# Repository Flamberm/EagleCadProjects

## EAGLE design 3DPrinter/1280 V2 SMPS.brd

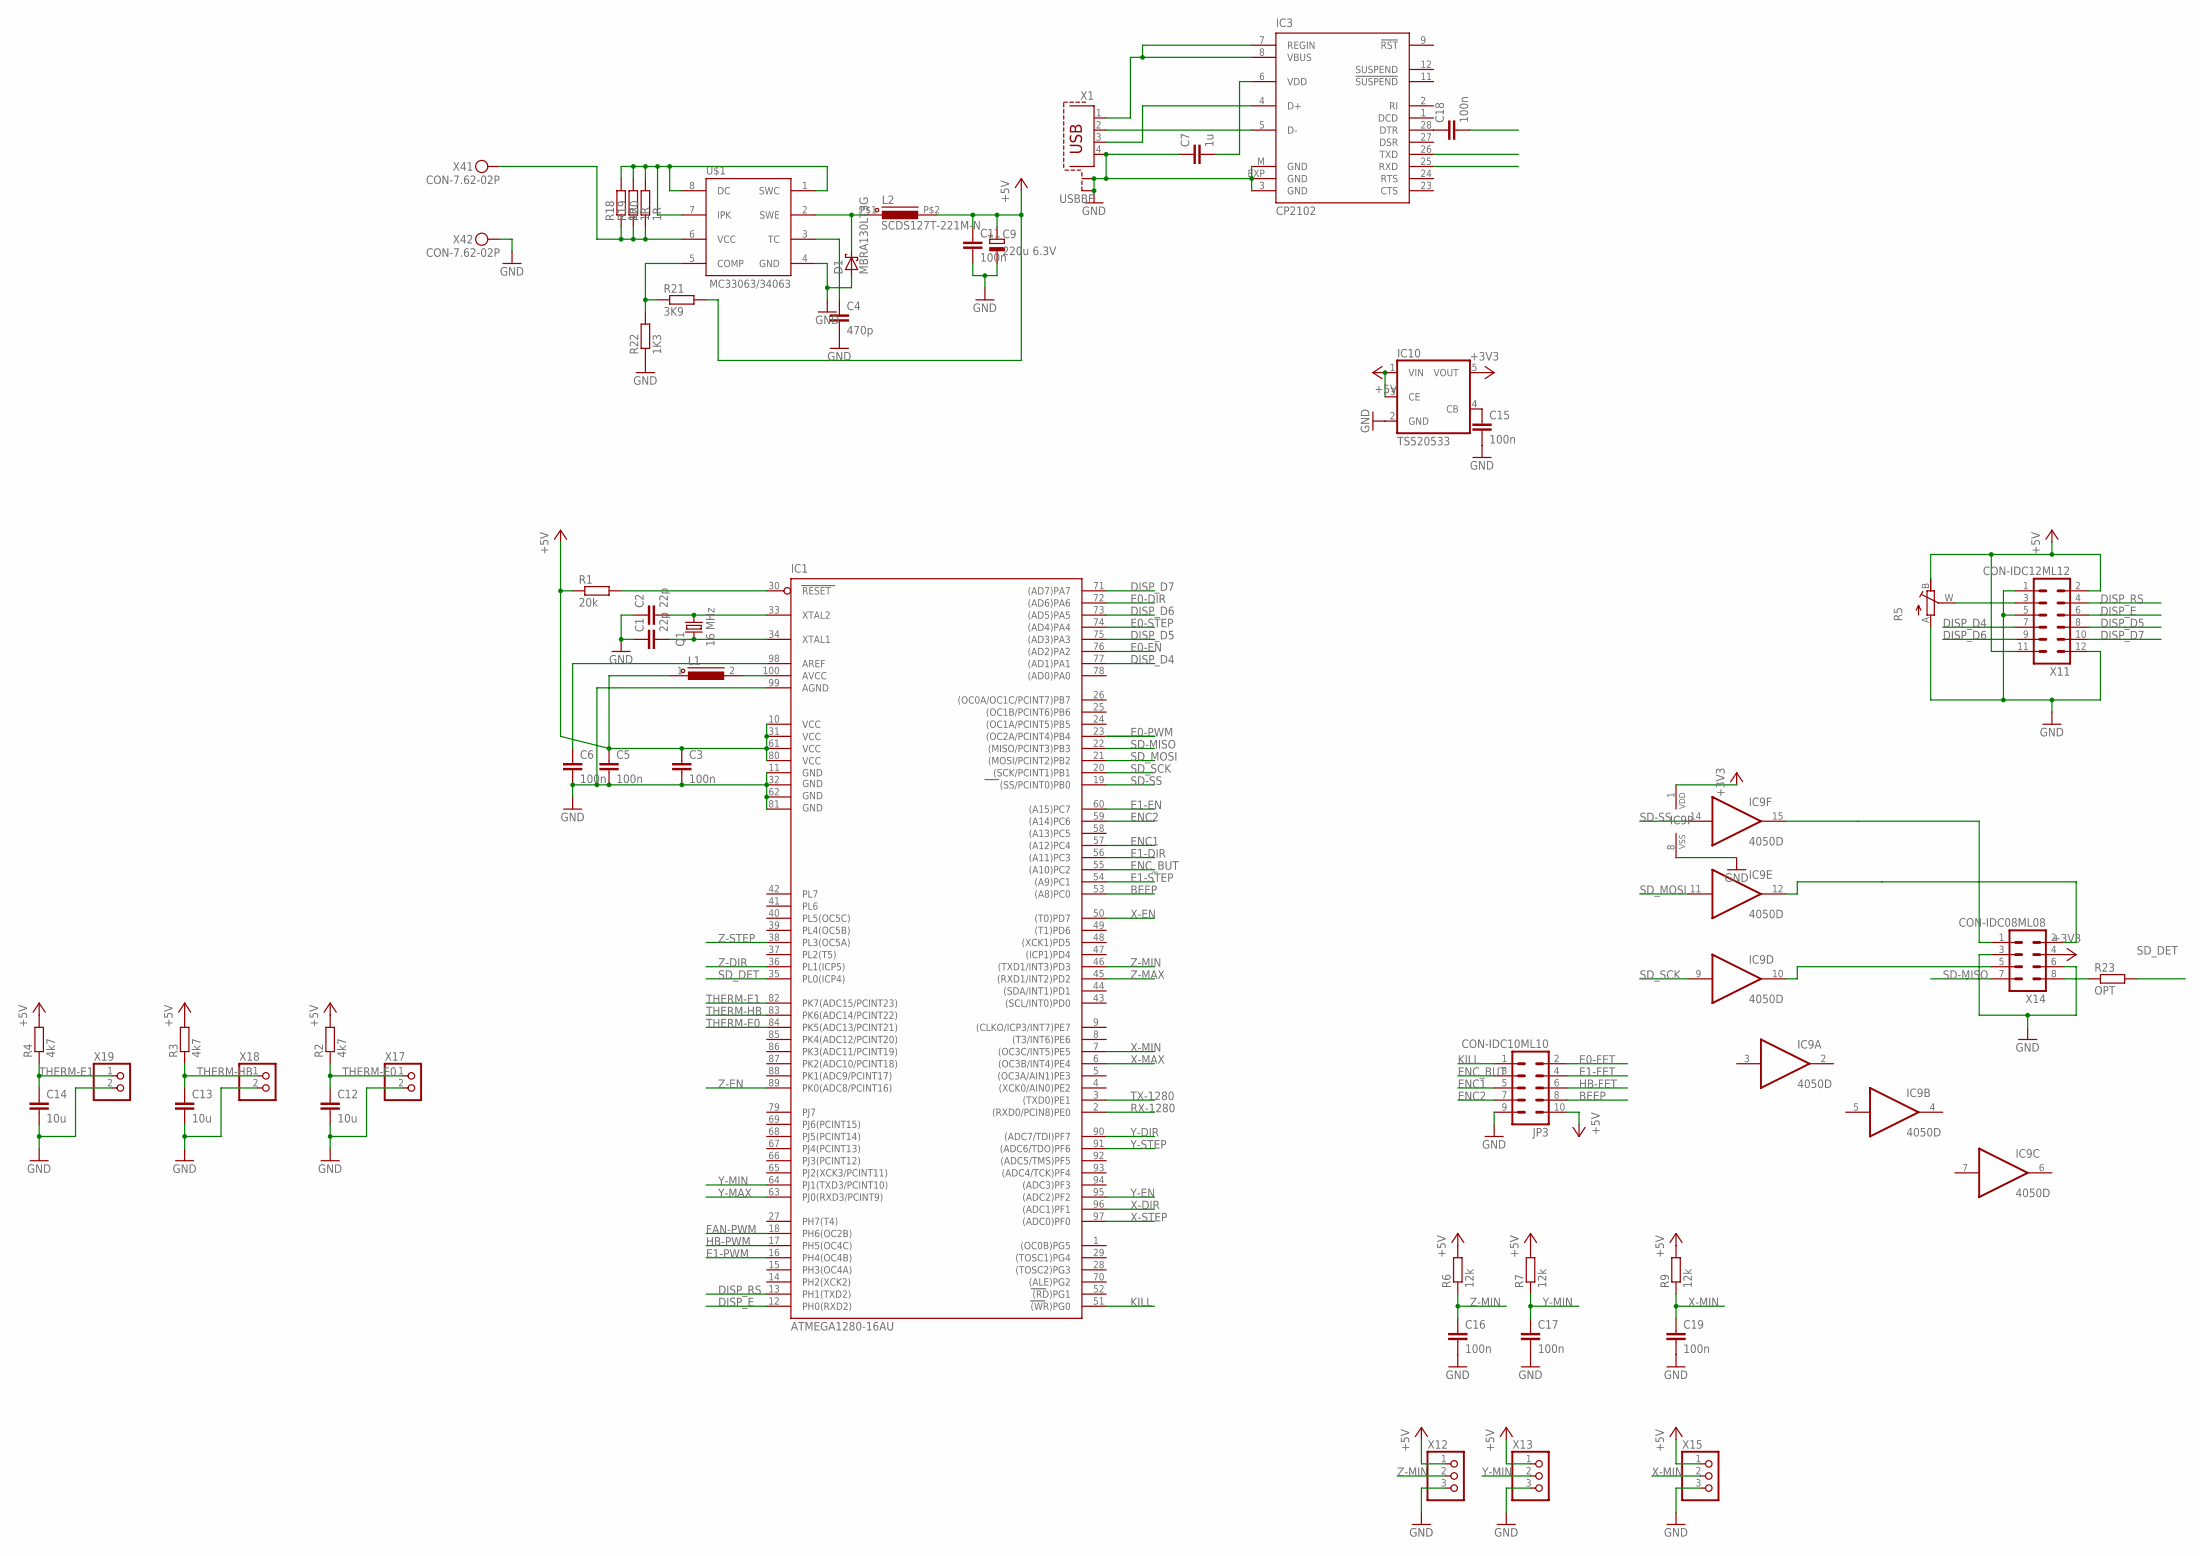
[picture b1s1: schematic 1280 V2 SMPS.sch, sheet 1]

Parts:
C1, C2: 22p; C0805
C3, C5, C6, C11, C15, C16, C17, C18, C19: 100n; C0805
C4: 470p; C0805
C7: 1u; C0805
C9: 220u 6.3V; 153CLV-0605
C12, C13, C14: 10u; C1210
D1: MBRA130LT3G; DO214AC
IC1: ATMEGA1280-16AU; TQFP100
IC3: CP2102; MLP28
IC9: 4050D; SO16
IC10: TS520533; SOT25
JP3: CON-IDC10ML10; ML10
L1: INDUCTOR1210; C1210
L2: SCDS127T-221M-N; SCD-0705
Q1: 16 MHz; CRYSTAL-3225
R1: 20k; R0805
R2, R3, R4: 4k7; R0805
R5: R_POTTURN-X; RJ9W
R6, R7, R9: 12k; R0805
R18, R19, R20: 1R; R0805
R21: 3K9; R0805
R22: 1K3; R0805
R23: OPT; R0805
U$1: MC33063/MC34063D; SO08
X1: USBBF; PN61729-S
X4: CON-7.62-02P; KF25C-7.62-02P-13
X11: CON-IDC12ML12; ML12
X12, X13, X15: PINHD-1X3; 1X03
X14: CON-IDC08ML08; ML08
X17, X18, X19: PINHD-1X2; 1X02

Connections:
!RST: C18.2, IC1.30 (RESET), R1.2
+3V3: IC9.1 (VDD), IC10.5 (VOUT), X14.4
+5V: C3.1, C5.1, C9.+, C11.1, IC1.10 (VCC), IC1.31 (VCC1), IC1.61 (VCC2), IC1.80 (VCC3), IC10.1 (VIN), IC10.3 (CE), JP3.10, L1.1, L2.P$2 (2), R1.1, R2.2, R3.2, R4.2, R5.B (E), R6.2, R7.2, R9.2, R21.2, X11.2, X11.11, X12.1, X13.1, X15.1; also elsewhere on the board
AREF: C6.1, IC1.98 (AREF)
AVCC: IC1.100 (AVCC), L1.2
BEEP: IC1.53 ((A8)PC0), JP3.8
DISP_D4: IC1.77 ((AD1)PA1), X11.7
DISP_D5: IC1.75 ((AD3)PA3), X11.8
DISP_D6: IC1.73 ((AD5)PA5), X11.9
DISP_D7: IC1.71 ((AD7)PA7), X11.10
DISP_E: IC1.12 (PH0(RXD2)), X11.6
DISP_RS: IC1.13 (PH1(TXD2)), X11.4
E0-DIR: IC1.72 ((AD6)PA6); also elsewhere on the board
E0-EN: IC1.76 ((AD2)PA2); also elsewhere on the board
E0-FET: JP3.2; also elsewhere on the board
E0-PWM: IC1.23 ((OC2A/PCINT4)PB4); also elsewhere on the board
E0-STEP: IC1.74 ((AD4)PA4); also elsewhere on the board
E1-DIR: IC1.56 ((A11)PC3); also elsewhere on the board
E1-EN: IC1.60 ((A15)PC7); also elsewhere on the board
E1-FET: JP3.4; also elsewhere on the board
E1-PWM: IC1.16 (PH4(OC4B)); also elsewhere on the board
E1-STEP: IC1.54 ((A9)PC1); also elsewhere on the board
ENC1: IC1.57 ((A12)PC4), JP3.5
ENC2: IC1.59 ((A14)PC6), JP3.7
ENC_BUT: IC1.55 ((A10)PC2), JP3.3
FAN-PWM: IC1.18 (PH6(OC2B)); also elsewhere on the board
GND: C1.1, C2.1, C3.2, C4.2, C5.2, C6.2, C7.1, C9.-, C11.2, C12.2, C13.2, C14.2, C15.2, C16.2, C17.2, C19.2, D1.A, IC1.11 (GND), IC1.32 (GND1), IC1.62 (GND2), IC1.81 (GND3), IC1.99 (AGND), IC3.3 (GND), IC3.EXP (GND), IC3.M (GND), IC9.8 (VSS), IC10.2 (GND), JP3.9, R5.A, R22.1, U$1.4 (GND), X1.4 (GND), X1.S1, X1.S2, X4.P$2, X11.1, X11.5, X11.12, X12.3, X13.3, X14.3, X14.6, X15.3, X17.2, X18.2, X19.2; also elsewhere on the board
HB-FET: JP3.6; also elsewhere on the board
HB-PWM: IC1.17 (PH5(OC4C)); also elsewhere on the board
KILL: IC1.51 ((WR)PG0), JP3.1
unnamed: IC3.5 (D-), X1.2 (D-)
unnamed: IC3.4 (D+), X1.3 (D+)
unnamed: C7.2, IC3.6 (VDD)
unnamed: C18.1, IC3.28 (DTR)
unnamed: IC3.7 (REGIN), IC3.8 (VBUS), X1.1 (VCC)
unnamed: R5.W (S), X11.3
unnamed: R23.1, X14.8
unnamed: IC9.15 (O), X14.1
unnamed: IC9.12 (O), X14.2
unnamed: IC9.10 (O), X14.5
unnamed: C15.1, IC10.4 (CB)
unnamed: R18.2, R19.2, R20.2, U$1.1 (SWC), U$1.7 (IPK), U$1.8 (DC)
unnamed: D1.C, L2.P$1 (1), U$1.2 (SWE)
unnamed: C4.1, U$1.3 (TC)
unnamed: R21.1, R22.2, U$1.5 (COMP)
RX-1280: IC1.2 ((RXD0/PCIN8)PE0), IC3.26 (TXD)
SD-MISO: IC1.22 ((MISO/PCINT3)PB3), X14.7
SD-SS: IC1.19 ((SS/PCINT0)PB0), IC9.14 (I)
SD_DET: IC1.35 (PL0(ICP4)), R23.2
SD_MOSI: IC1.21 ((MOSI/PCINT2)PB2), IC9.11 (I)
SD_SCK: IC1.20 ((SCK/PCINT1)PB1), IC9.9 (I)
THERM-E0: C12.1, IC1.84 (PK5(ADC13/PCINT21)), R2.1, X17.1
THERM-E1: C14.1, IC1.82 (PK7(ADC15/PCINT23)), R4.1, X19.1
THERM-HB: C13.1, IC1.83 (PK6(ADC14/PCINT22)), R3.1, X18.1
TX-1280: IC1.3 ((TXD0)PE1), IC3.25 (RXD)
V-IN: R18.1, R19.1, R20.1, U$1.6 (VCC), X4.P$1; also elsewhere on the board
X-DIR: IC1.96 ((ADC1)PF1); also elsewhere on the board
X-EN: IC1.50 ((T0)PD7); also elsewhere on the board
X-MAX: IC1.6 ((OC3B/INT4)PE4)
X-MIN: C19.1, IC1.7 ((OC3C/INT5)PE5), R9.1, X15.2
X-STEP: IC1.97 ((ADC0)PF0); also elsewhere on the board
XTAL1: C1.2, IC1.34 (XTAL1), Q1.P$2 (1)
XTAL2: C2.2, IC1.33 (XTAL2), Q1.P$4 (2)
Y-DIR: IC1.90 ((ADC7/TDI)PF7); also elsewhere on the board
Y-EN: IC1.95 ((ADC2)PF2); also elsewhere on the board
Y-MAX: IC1.63 (PJ0(RXD3/PCINT9))
Y-MIN: C17.1, IC1.64 (PJ1(TXD3/PCINT10)), R7.1, X13.2
Y-STEP: IC1.91 ((ADC6/TDO)PF6); also elsewhere on the board
Z-DIR: IC1.36 (PL1(ICP5)); also elsewhere on the board
Z-EN: IC1.89 (PK0(ADC8/PCINT16)); also elsewhere on the board
Z-MAX: IC1.45 ((RXD1/INT2)PD2)
Z-MIN: C16.1, IC1.46 ((TXD1/INT3)PD3), R6.1, X12.2
Z-STEP: IC1.38 (PL3(OC5A)); also elsewhere on the board

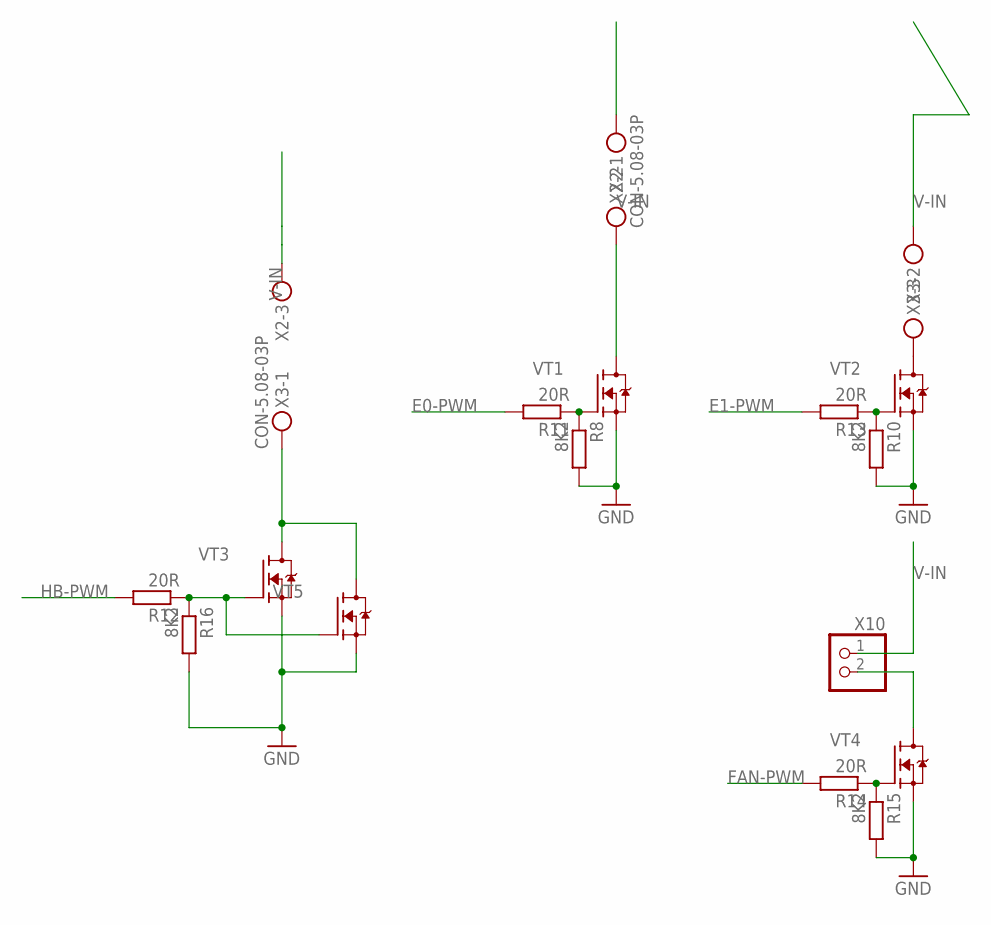
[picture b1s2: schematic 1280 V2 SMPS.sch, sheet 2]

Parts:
R8, R10, R15, R16: 8K2; R0805
R11, R12, R13, R14: 20R; R0805
VT1, VT2, VT3, VT4, VT5: FET-NPF-6X5; POWERFLAT-5X6
X2, X3: CON-5.08-03P; MKDSN1,5/3-5,08
X10: PINHD-1X2; 1X02

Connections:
E0-: VT1.D1 (D), X2.2
E0-FET: R8.1, R11.1, VT1.G; also elsewhere on the board
E0-PWM: R11.2; also elsewhere on the board
E1-FET: R10.1, R13.1, VT2.G; also elsewhere on the board
E1-PWM: R13.2; also elsewhere on the board
FAN-: VT4.D1 (D), X10.2
FAN-PWM: R14.2; also elsewhere on the board
GND: R8.2, R10.2, R15.2, R16.2, VT1.S1 (S), VT1.S2 (S), VT1.S3 (S), VT2.S1 (S), VT2.S2 (S), VT2.S3 (S), VT3.S1 (S), VT3.S2 (S), VT3.S3 (S), VT4.S1 (S), VT4.S2 (S), VT4.S3 (S), VT5.S1 (S), VT5.S2 (S), VT5.S3 (S); also elsewhere on the board
HB-: VT3.D1 (D), VT5.D1 (D), X3.1
HB-FET: R12.1, R16.1, VT3.G, VT5.G; also elsewhere on the board
HB-PWM: R12.2; also elsewhere on the board
unnamed: R14.1, R15.1, VT4.G
unnamed: VT2.D1 (D), X3.3
V-IN: X2.1, X2.3, X3.2, X10.1; also elsewhere on the board

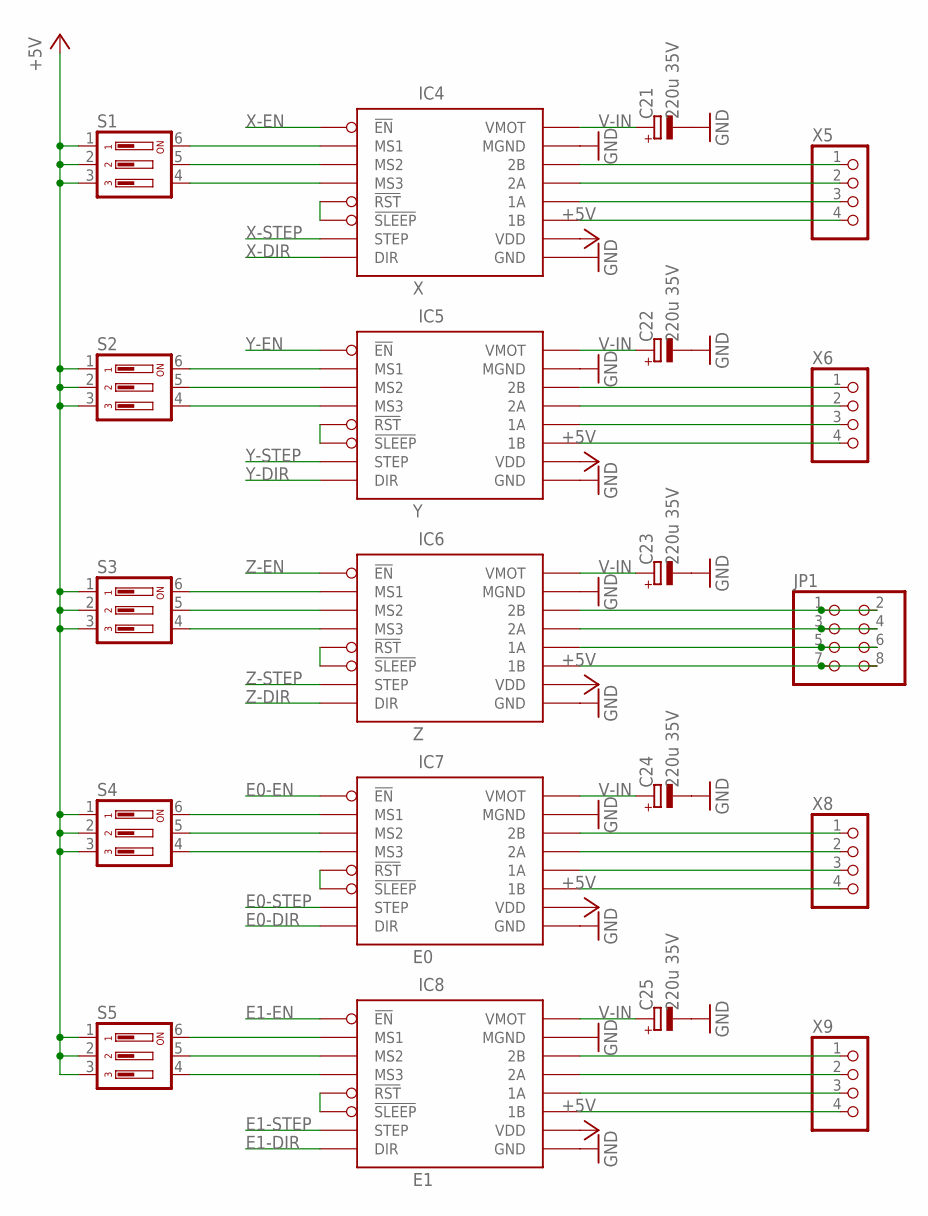
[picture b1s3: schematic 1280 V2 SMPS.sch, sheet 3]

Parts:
C21, C22, C23, C24, C25: 220u 35V; E3.5-8-11H
IC4: X; DRV-BRK
IC5: Y; DRV-BRK
IC6: Z; DRV-BRK
IC7: E0; DRV-BRK
IC8: E1; DRV-BRK
JP1: PINHD-2X4/90; 2X04/90
S1, S2, S3, S4, S5: SW-DIP03S; DIP03YL
X5, X6, X8, X9: PINHD-1X4/90; 1X04/90

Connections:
+5V: IC4.P$10 (VDD), IC5.P$10 (VDD), IC6.P$10 (VDD), IC7.P$10 (VDD), IC8.P$10 (VDD), S1.1, S1.2, S1.3, S2.1, S2.2, S2.3, S3.1, S3.2, S3.3, S4.1, S4.2, S4.3, S5.1, S5.2, S5.3; also elsewhere on the board
E0-DIR: IC7.P$8 (DIR); also elsewhere on the board
E0-EN: IC7.P$1 (!EN); also elsewhere on the board
E0-STEP: IC7.P$7 (STEP); also elsewhere on the board
E1-DIR: IC8.P$8 (DIR); also elsewhere on the board
E1-EN: IC8.P$1 (!EN); also elsewhere on the board
E1-STEP: IC8.P$7 (STEP); also elsewhere on the board
GND: C21.-, C22.-, C23.-, C24.-, C25.-, IC4.P$9 (GND), IC4.P$15 (MGND), IC5.P$9 (GND), IC5.P$15 (MGND), IC6.P$9 (GND), IC6.P$15 (MGND), IC7.P$9 (GND), IC7.P$15 (MGND), IC8.P$9 (GND), IC8.P$15 (MGND); also elsewhere on the board
unnamed: IC4.P$14 (2B), X5.1
unnamed: IC4.P$13 (2A), X5.2
unnamed: IC4.P$12 (1A), X5.3
unnamed: IC4.P$5 (!RST), IC4.P$6 (!SLEEP)
unnamed: IC5.P$5 (!RST), IC5.P$6 (!SLEEP)
unnamed: IC4.P$11 (1B), X5.4
unnamed: IC7.P$5 (!RST), IC7.P$6 (!SLEEP)
unnamed: IC6.P$5 (!RST), IC6.P$6 (!SLEEP)
unnamed: IC5.P$14 (2B), X6.1
unnamed: IC5.P$13 (2A), X6.2
unnamed: IC8.P$5 (!RST), IC8.P$6 (!SLEEP)
unnamed: IC5.P$12 (1A), X6.3
unnamed: IC5.P$11 (1B), X6.4
unnamed: IC6.P$14 (2B), JP1.1, JP1.2
unnamed: IC6.P$13 (2A), JP1.3, JP1.4
unnamed: IC6.P$12 (1A), JP1.5, JP1.6
unnamed: IC6.P$11 (1B), JP1.7, JP1.8
unnamed: IC7.P$14 (2B), X8.1
unnamed: IC7.P$13 (2A), X8.2
unnamed: IC7.P$12 (1A), X8.3
unnamed: IC7.P$11 (1B), X8.4
unnamed: IC8.P$14 (2B), X9.1
unnamed: IC8.P$13 (2A), X9.2
unnamed: IC8.P$12 (1A), X9.3
unnamed: IC8.P$11 (1B), X9.4
unnamed: IC4.P$4 (MS3), S1.4
unnamed: IC4.P$3 (MS2), S1.5
unnamed: IC4.P$2 (MS1), S1.6
unnamed: IC5.P$2 (MS1), S2.6
unnamed: IC5.P$3 (MS2), S2.5
unnamed: IC5.P$4 (MS3), S2.4
unnamed: IC6.P$2 (MS1), S3.6
unnamed: IC6.P$3 (MS2), S3.5
unnamed: IC6.P$4 (MS3), S3.4
unnamed: IC7.P$2 (MS1), S4.6
unnamed: IC7.P$3 (MS2), S4.5
unnamed: IC7.P$4 (MS3), S4.4
unnamed: IC8.P$2 (MS1), S5.6
unnamed: IC8.P$3 (MS2), S5.5
unnamed: IC8.P$4 (MS3), S5.4
V-IN: C21.+, C22.+, C23.+, C24.+, C25.+, IC4.P$16 (VMOT), IC5.P$16 (VMOT), IC6.P$16 (VMOT), IC7.P$16 (VMOT), IC8.P$16 (VMOT); also elsewhere on the board
X-DIR: IC4.P$8 (DIR); also elsewhere on the board
X-EN: IC4.P$1 (!EN); also elsewhere on the board
X-STEP: IC4.P$7 (STEP); also elsewhere on the board
Y-DIR: IC5.P$8 (DIR); also elsewhere on the board
Y-EN: IC5.P$1 (!EN); also elsewhere on the board
Y-STEP: IC5.P$7 (STEP); also elsewhere on the board
Z-DIR: IC6.P$8 (DIR); also elsewhere on the board
Z-EN: IC6.P$1 (!EN); also elsewhere on the board
Z-STEP: IC6.P$7 (STEP); also elsewhere on the board

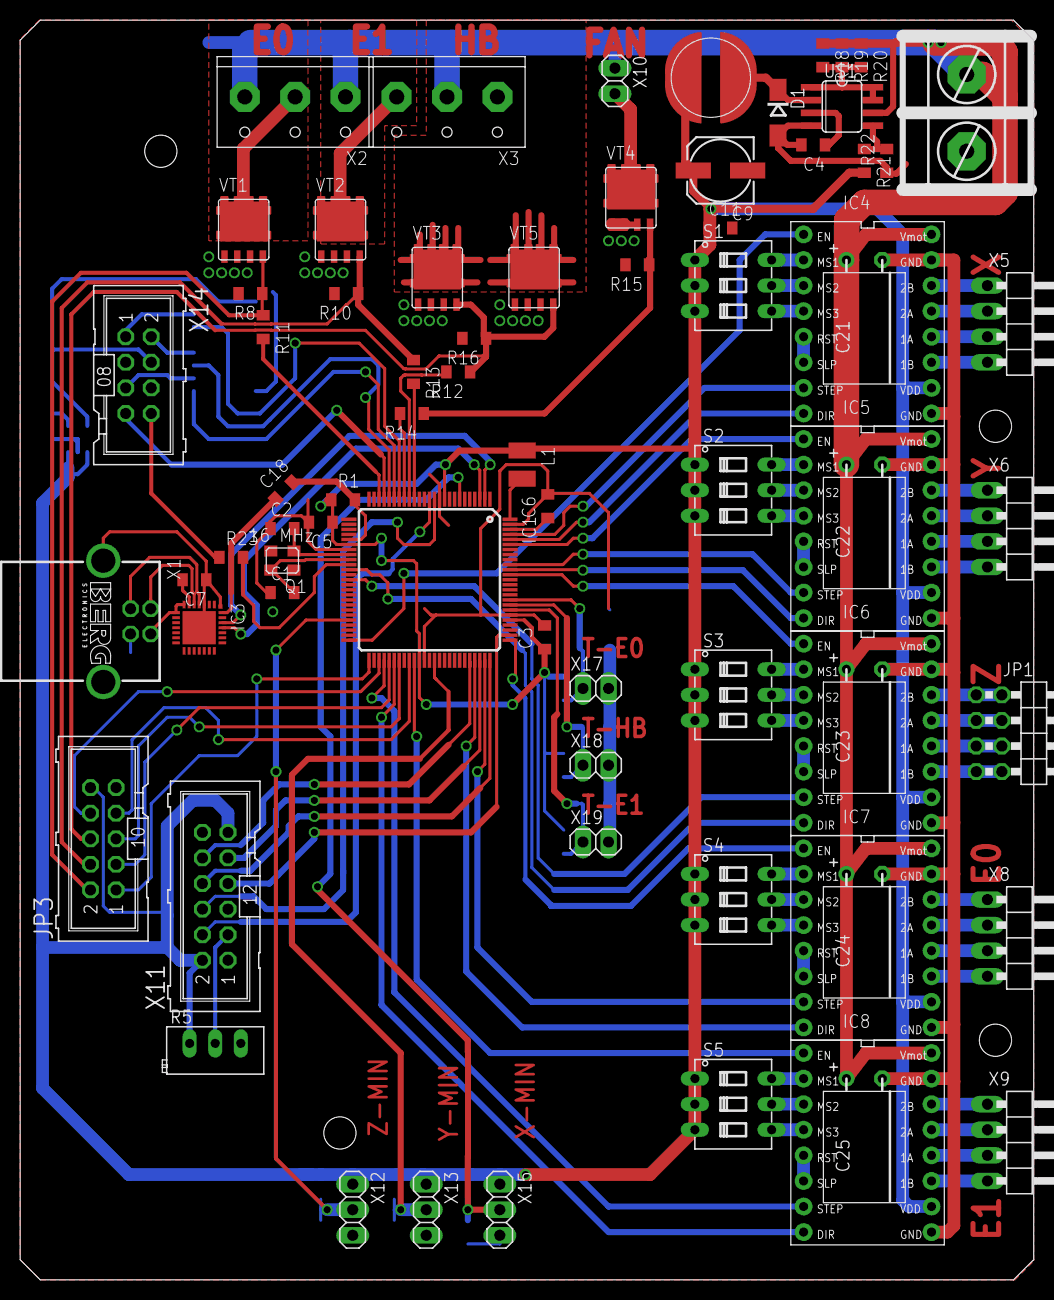
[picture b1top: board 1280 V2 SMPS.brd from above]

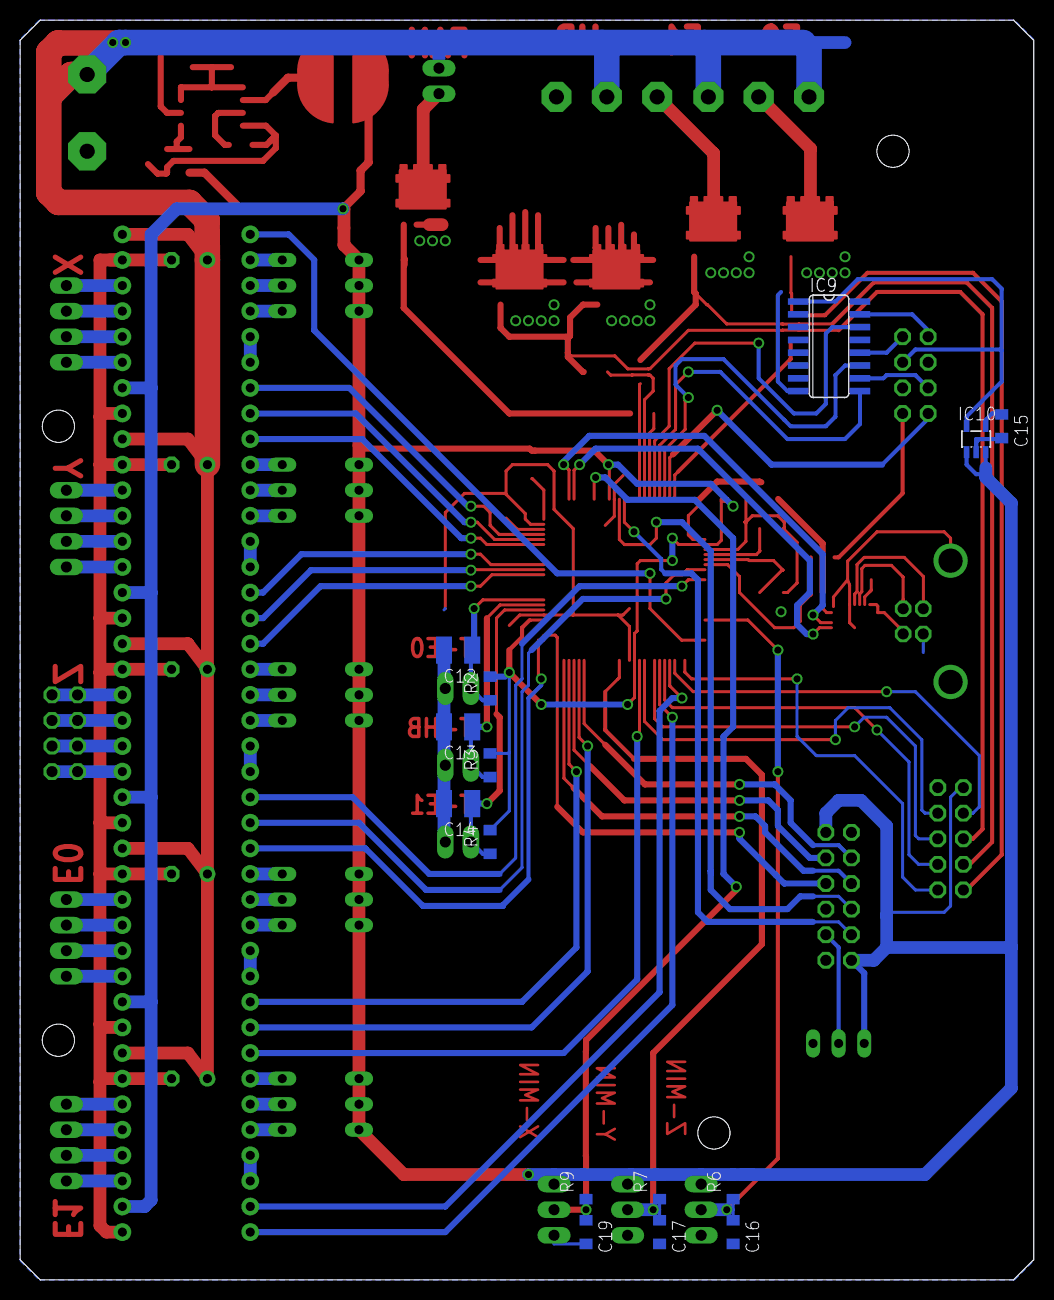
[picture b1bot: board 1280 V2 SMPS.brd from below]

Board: 2 copper layers, 100.6 x 125.1 mm, 87 parts (15 on the bottom side), 115 nets.

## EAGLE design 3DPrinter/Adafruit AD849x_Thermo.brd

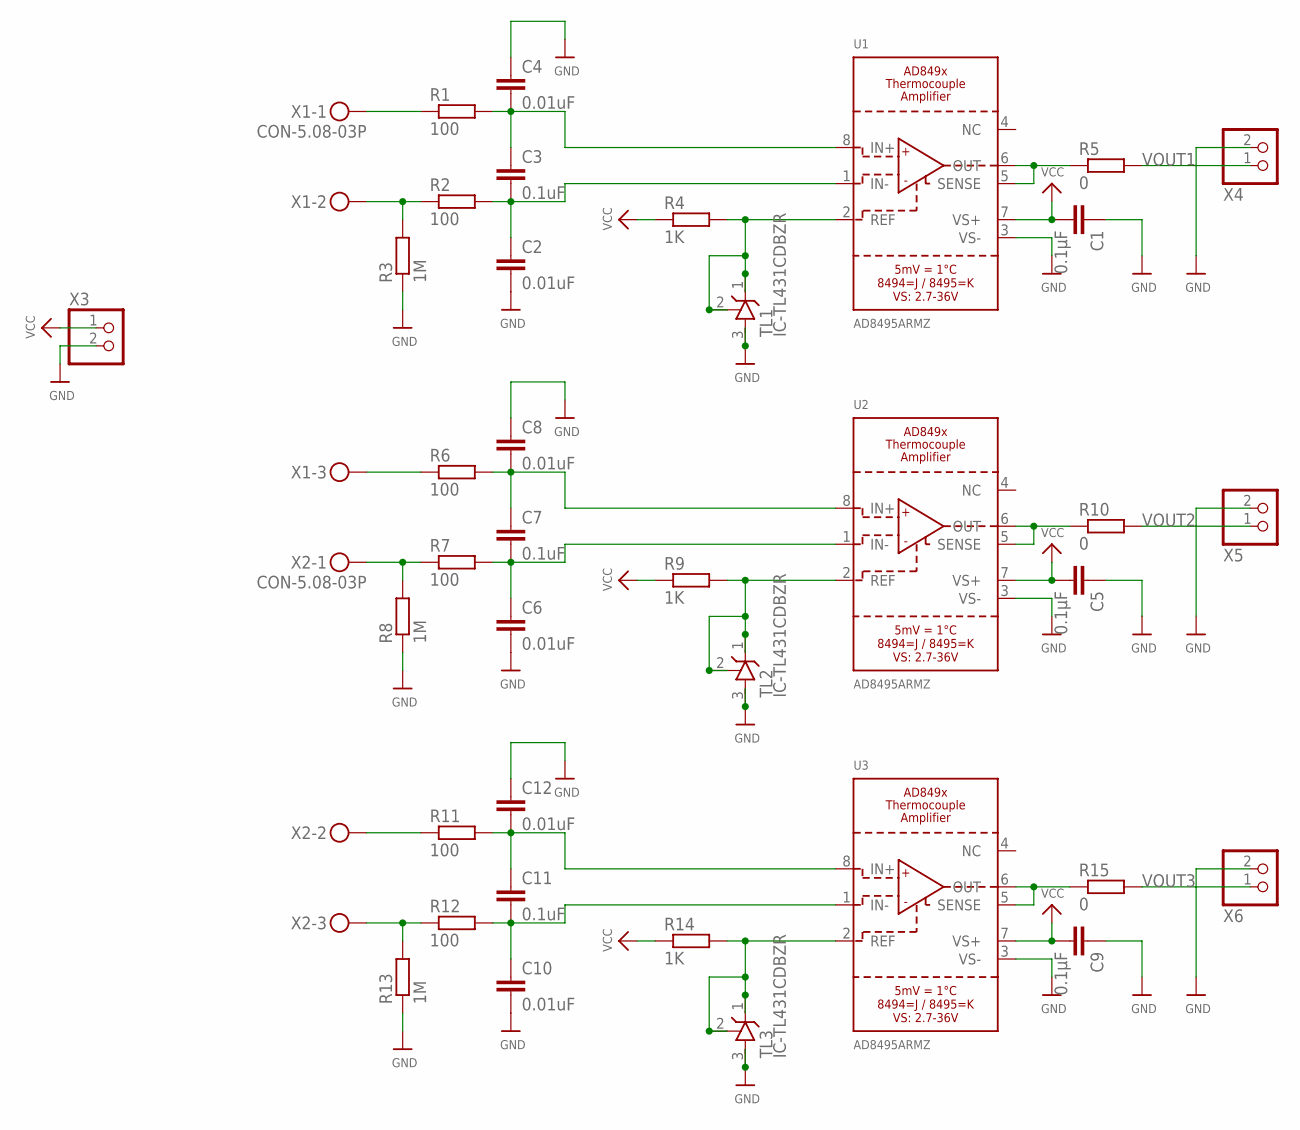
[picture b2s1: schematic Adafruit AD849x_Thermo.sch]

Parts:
C1, C5, C9: 0.1µF; C0805
C2, C4, C6, C8, C10, C12: 0.01uF; C0805
C3, C7, C11: 0.1uF; C0805
R1, R2, R6, R7, R11, R12: 100; R0805
R3, R8, R13: 1M; R0805
R4, R9, R14: 1K; R0805
R5, R10, R15: 0; R0805
TL1, TL2, TL3: IC-TL431CDBZR; SOT23
U1, U2, U3: AD8495ARMZ; MSOP8_0.65MM
X1, X2: CON-5.08-03P; MKDSN1,5/3-5,08
X3, X4, X5, X6: CON-CP-02; CON-CT-02

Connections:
GND: C1.1, C2.2, C4.1, C5.1, C6.2, C8.1, C9.1, C10.2, C12.1, R3.1, R8.1, R13.1, TL1.3 (A), TL2.3 (A), TL3.3 (A), U1.3 (VS-), U2.3 (VS-), U3.3 (VS-), X3.2, X4.2, X5.2, X6.2
IN+: R1.1, X1.1
IN+1: R6.1, X1.3
IN+2: R11.1, X2.2
IN-: R2.1, R3.2, X1.2
IN-1: R7.1, R8.2, X2.1
IN-2: R12.1, R13.2, X2.3
unnamed: R4.2, TL1.1 (C), TL1.2 (R), U1.2 (REF)
unnamed: C3.1, C4.2, R1.2, U1.8 (IN+)
unnamed: C2.1, C3.2, R2.2, U1.1 (IN-)
unnamed: R5.2, X4.1
unnamed: C7.1, C8.2, R6.2, U2.8 (IN+)
unnamed: C6.1, C7.2, R7.2, U2.1 (IN-)
unnamed: R9.2, TL2.1 (C), TL2.2 (R), U2.2 (REF)
unnamed: R10.2, X5.1
unnamed: C11.1, C12.2, R11.2, U3.8 (IN+)
unnamed: C10.1, C11.2, R12.2, U3.1 (IN-)
unnamed: R14.2, TL3.1 (C), TL3.2 (R), U3.2 (REF)
unnamed: R15.2, X6.1
VCC: C1.2, C5.2, C9.2, R4.1, R9.1, R14.1, U1.7 (VS+), U2.7 (VS+), U3.7 (VS+), X3.1
VOUT1: R5.1, U1.5 (SENSE), U1.6 (OUT)
VOUT2: R10.1, U2.5 (SENSE), U2.6 (OUT)
VOUT3: R15.1, U3.5 (SENSE), U3.6 (OUT)

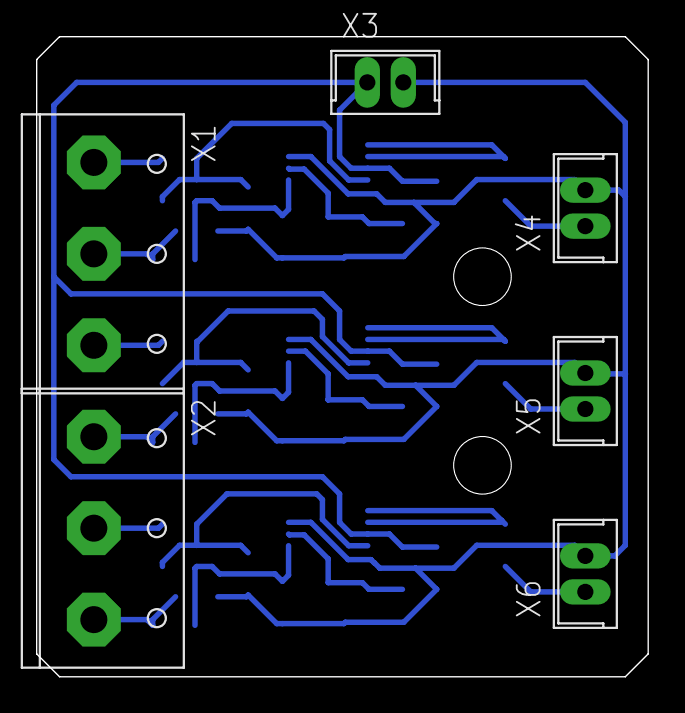
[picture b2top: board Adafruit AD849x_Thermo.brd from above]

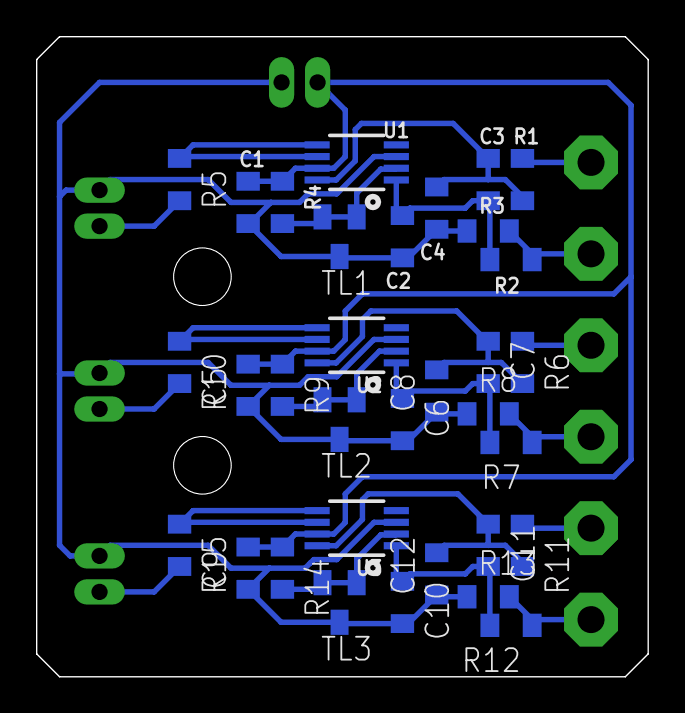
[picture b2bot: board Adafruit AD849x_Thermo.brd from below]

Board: 2 copper layers, 34.0 x 35.6 mm, 39 parts (33 on the bottom side), 23 nets.

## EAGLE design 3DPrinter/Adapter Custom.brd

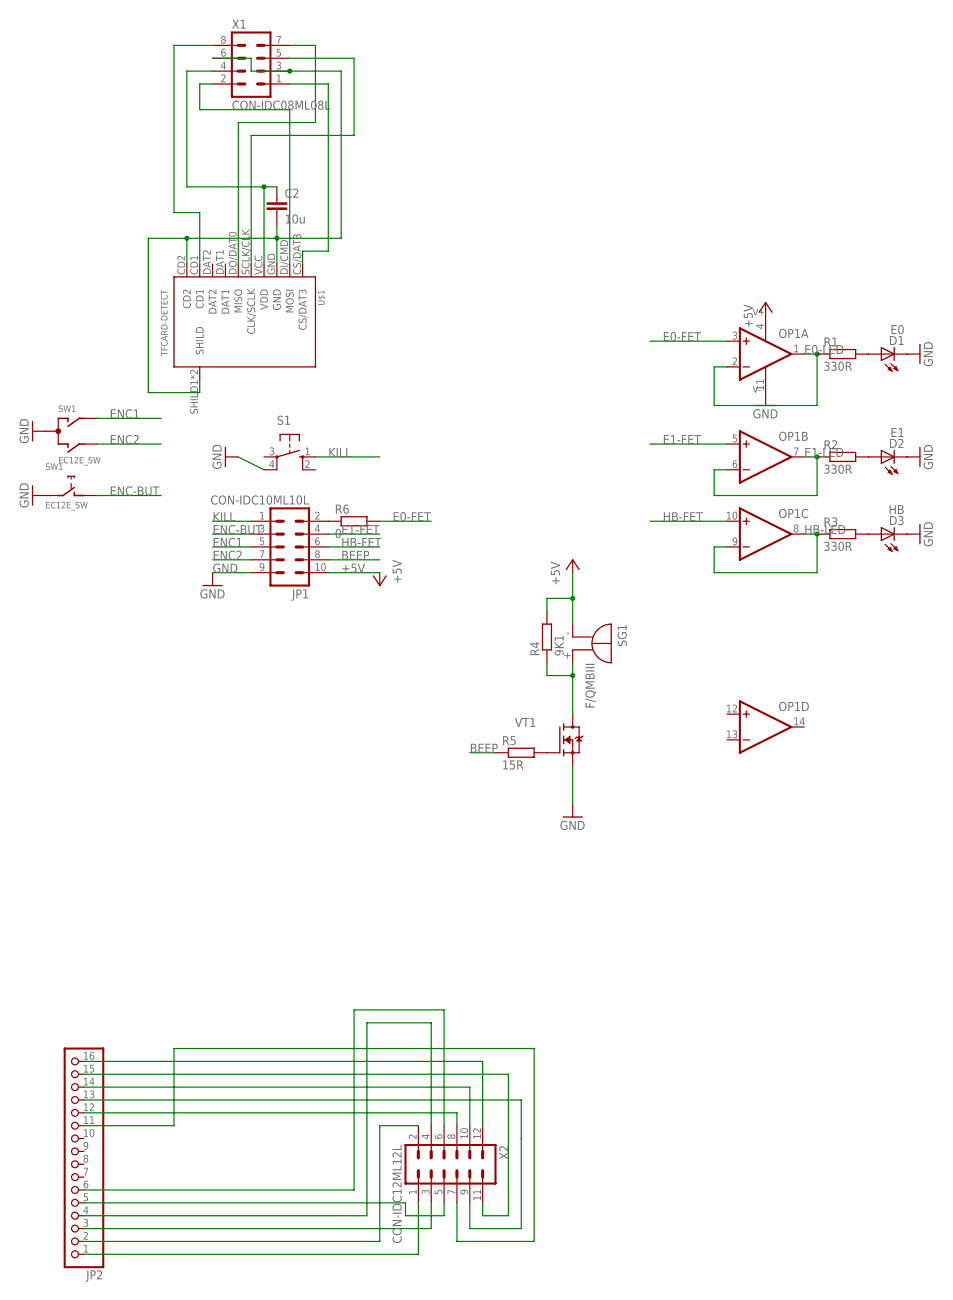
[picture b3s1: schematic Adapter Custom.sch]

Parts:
C2: 10u; C0805
D1: E0; LED3MM
D2: E1; LED3MM
D3: HB; LED3MM
JP1: CON-IDC10ML10L; ML10L
JP2: PINHD-1X16; 1X16
OP1: OP-AMP-4LMV324IPT; TSSOP14
R1, R2, R3: 330R; R0805
R4: 9K1; R0805
R5: 15R; R0805
R6: 0; R0805
S1: 40-XX; B3F-40XX
SG1: F/QMBIII
SW1: EC12E_SW; ALPS_EC12E_SW
U$1: TFCARD-DETECT; ST-TF-DETECT
VT1: FET-NSOT-23; SOT23
X1: CON-IDC08ML08L; ML08L
X2: CON-IDC12ML12L; ML12L

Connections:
+5V: JP1.10, OP1.4 (V+), R4.2, SG1.- (+)
BEEP: JP1.8, R5.1
E0-FET: OP1.3 (+IN), R6.2
E0-LED: OP1.1 (OUT), OP1.2 (-IN), R1.1
E1-FET: JP1.4, OP1.5 (+IN)
E1-LED: OP1.6 (-IN), OP1.7 (OUT), R2.1
ENC1: JP1.5, SW1.A
ENC2: JP1.7, SW1.B
ENC-BUT: JP1.3, SW1.D (1)
GND: D1.K (C), D2.K (C), D3.K (C), JP1.9, OP1.11 (V-), S1.4 (P1), SW1.C, SW1.E (2), VT1.2 (S)
HB-FET: JP1.6, OP1.10 (+IN)
HB-LED: OP1.8 (OUT), OP1.9 (-IN), R3.1
KILL: JP1.1, S1.1 (S)
unnamed: D1.A, R1.2
unnamed: D2.A, R2.2
unnamed: D3.A, R3.2
unnamed: R5.2, VT1.1 (G)
unnamed: R4.1, SG1.+ (-), VT1.3 (D)
unnamed: JP1.2, R6.1
unnamed: C2.2, U$1.CD2, U$1.GND, U$1.SHILD1 (SHILD), U$1.SHILD2 (SHILD), X1.3, X1.6
unnamed: C2.1, U$1.VCC (VDD), X1.4
unnamed: U$1.CS/DAT3, X1.1
unnamed: U$1.DI/CMD (MOSI), X1.2
unnamed: JP2.16, X2.12
unnamed: JP2.15, X2.11
unnamed: U$1.SCLK/CLK (CLK/SCLK), X1.5
unnamed: JP2.14, X2.10
unnamed: U$1.DO/DAT0 (MISO), X1.7
unnamed: JP2.12, X2.8
unnamed: JP2.13, X2.9
unnamed: JP2.11, X2.7
unnamed: JP2.1, X2.1
unnamed: JP2.2, X2.2
unnamed: JP2.3, X2.3
unnamed: JP2.5, X2.5
unnamed: JP2.4, X2.4
unnamed: JP2.6, X2.6
unnamed: U$1.CD1, X1.8

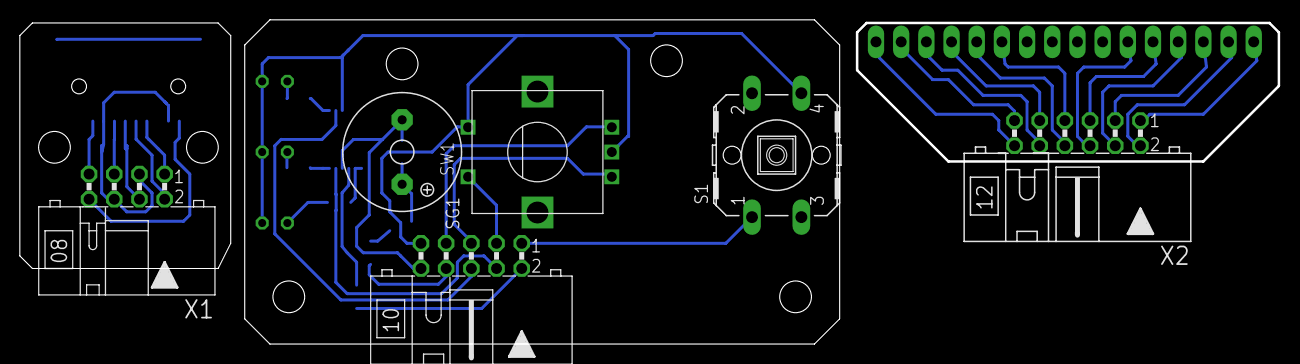
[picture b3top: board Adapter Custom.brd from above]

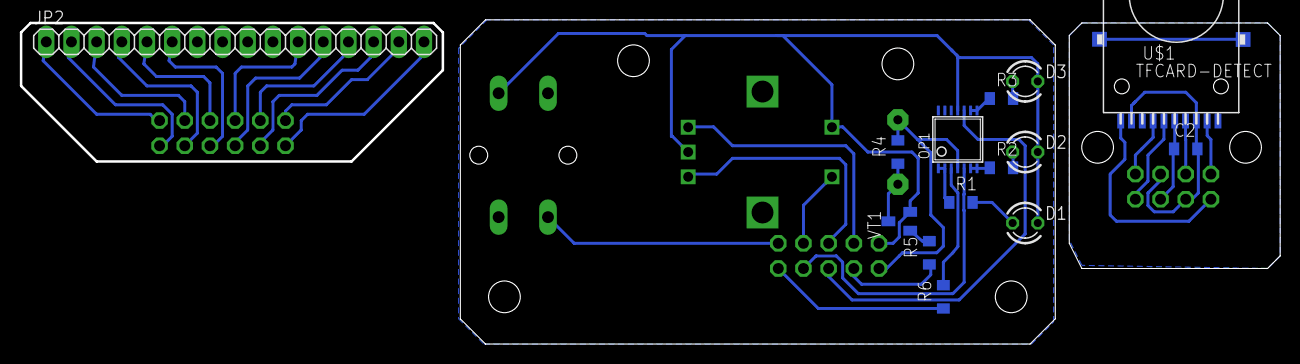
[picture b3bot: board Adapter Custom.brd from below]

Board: 2 copper layers, 127.0 x 32.7 mm, 20 parts (14 on the bottom side), 38 nets.

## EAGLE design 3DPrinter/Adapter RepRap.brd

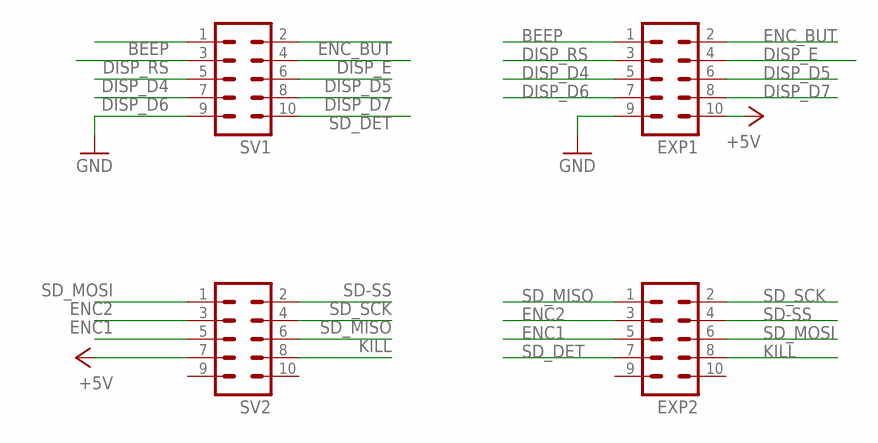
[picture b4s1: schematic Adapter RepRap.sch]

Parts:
EXP1, EXP2: ML10
SV1, SV2: ML10

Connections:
+5V: EXP1.10, SV2.7
BEEP: EXP1.1, SV1.1
DISP_D4: EXP1.5, SV1.5
DISP_D5: EXP1.6, SV1.6
DISP_D6: EXP1.7, SV1.7
DISP_D7: EXP1.8, SV1.8
DISP_E: EXP1.4, SV1.4
DISP_RS: EXP1.3, SV1.3
ENC1: EXP2.5, SV2.5
ENC2: EXP2.3, SV2.3
ENC_BUT: EXP1.2, SV1.2
GND: EXP1.9, SV1.9
KILL: EXP2.8, SV2.8
SD-SS: EXP2.4, SV2.2
SD_DET: EXP2.7, SV1.10
SD_MISO: EXP2.1, SV2.6
SD_MOSI: EXP2.6, SV2.1
SD_SCK: EXP2.2, SV2.4

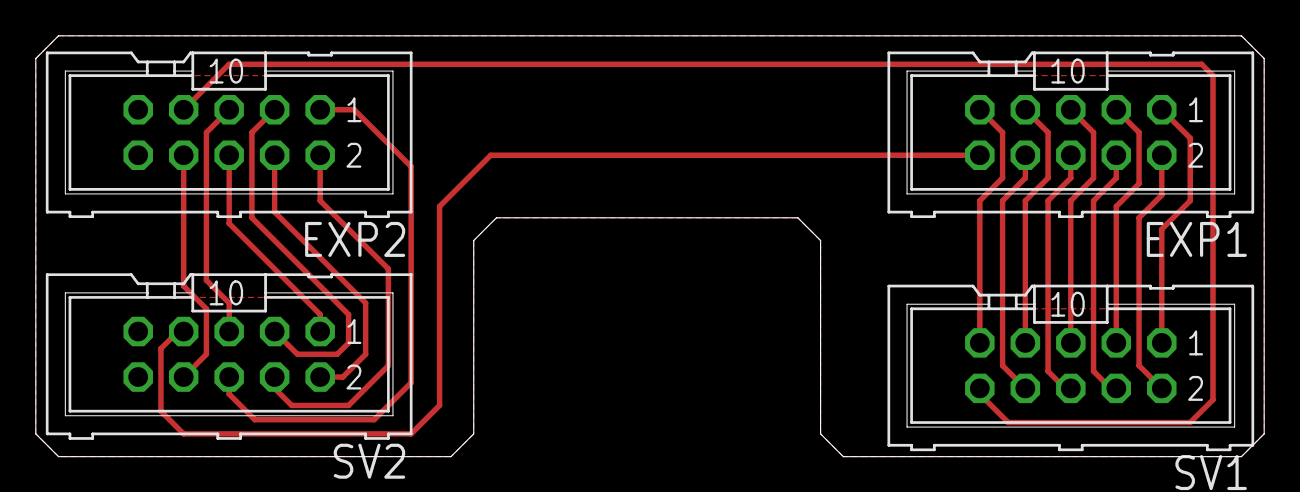
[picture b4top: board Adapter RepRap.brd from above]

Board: 2 copper layers, 68.6 x 23.5 mm, 4 parts (0 on the bottom side), 18 nets.

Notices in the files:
parts and their libraries:
microbuilder: This work is placed in the public domain, and may be freely used for commercial and non-commercial work with the following conditions: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
